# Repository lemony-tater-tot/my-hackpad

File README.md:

# my-hackpad
My hackpad made for hackclub stardance!

**Final Project design**

**Schematic**

**PCB Layout**

**Case**

# Bill of Materials (BOM)

| Part | Qty | Description / Specifications |
| :--- | :---: | :--- |
| **Seeed XIAO RP2040 microcontroller** | 1 | Main controller board |
| **EC11 rotary encoders (20mm D-shaft)** | 1 | Rotary input with integrated push-switch |
| **MX-style mechanical switches** | 3 | Key switches for macro inputs |
| **Blank DSA keycaps** | 3 | 1u profile keycaps for the mechanical switches |
| **Custom Macro Pad PCB** | 1 | Custom KiCad routed circuit board |
| **Switch Plate & Enclosure** | 1 | 3d printed top-plate / 3D printed housing |
| **M3×16mm screws** | 4 | Structural case assembly fasteners |
| **M3×5×4mm heatset inserts** | 4 | Brass inserts for secure case threading |

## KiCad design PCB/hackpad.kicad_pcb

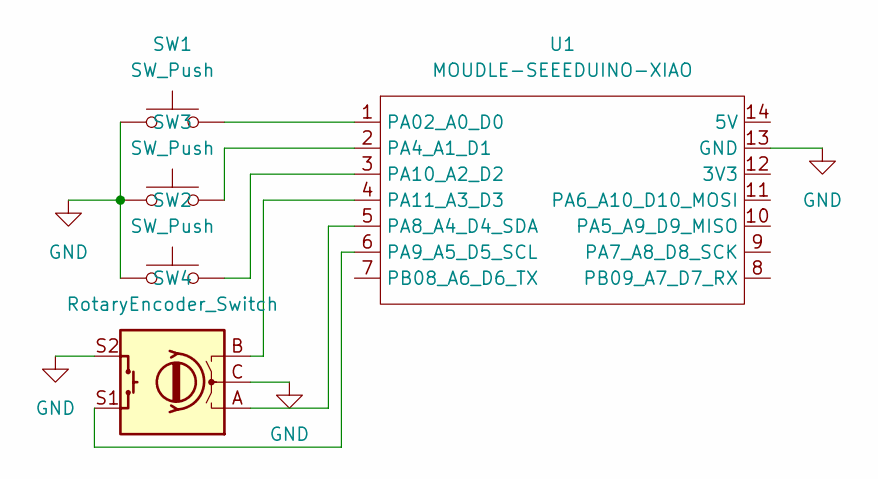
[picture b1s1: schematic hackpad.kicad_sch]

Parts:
SW1, SW2, SW3: SW_Push; SW_Cherry_MX_1.00u_PCB
SW4: RotaryEncoder_Switch; RotaryEncoder_Alps_EC11E-Switch_Vertical_H20mm
U1: MOUDLE-SEEEDUINO-XIAO; XIAO-Generic-Hybrid-14P-2.54-21X17.8MM

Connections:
GND: SW1.1, SW2.1, SW3.1, SW4.C, SW4.S2, U1.13 (GND)
unnamed: SW1.2, U1.1 (PA02_A0_D0)
unnamed: SW3.2, U1.2 (PA4_A1_D1)
unnamed: SW4.A, U1.5 (PA8_A4_D4_SDA)
unnamed: SW4.S1, U1.6 (PA9_A5_D5_SCL)
unnamed: SW2.2, U1.3 (PA10_A2_D2)
unnamed: SW4.B, U1.4 (PA11_A3_D3)

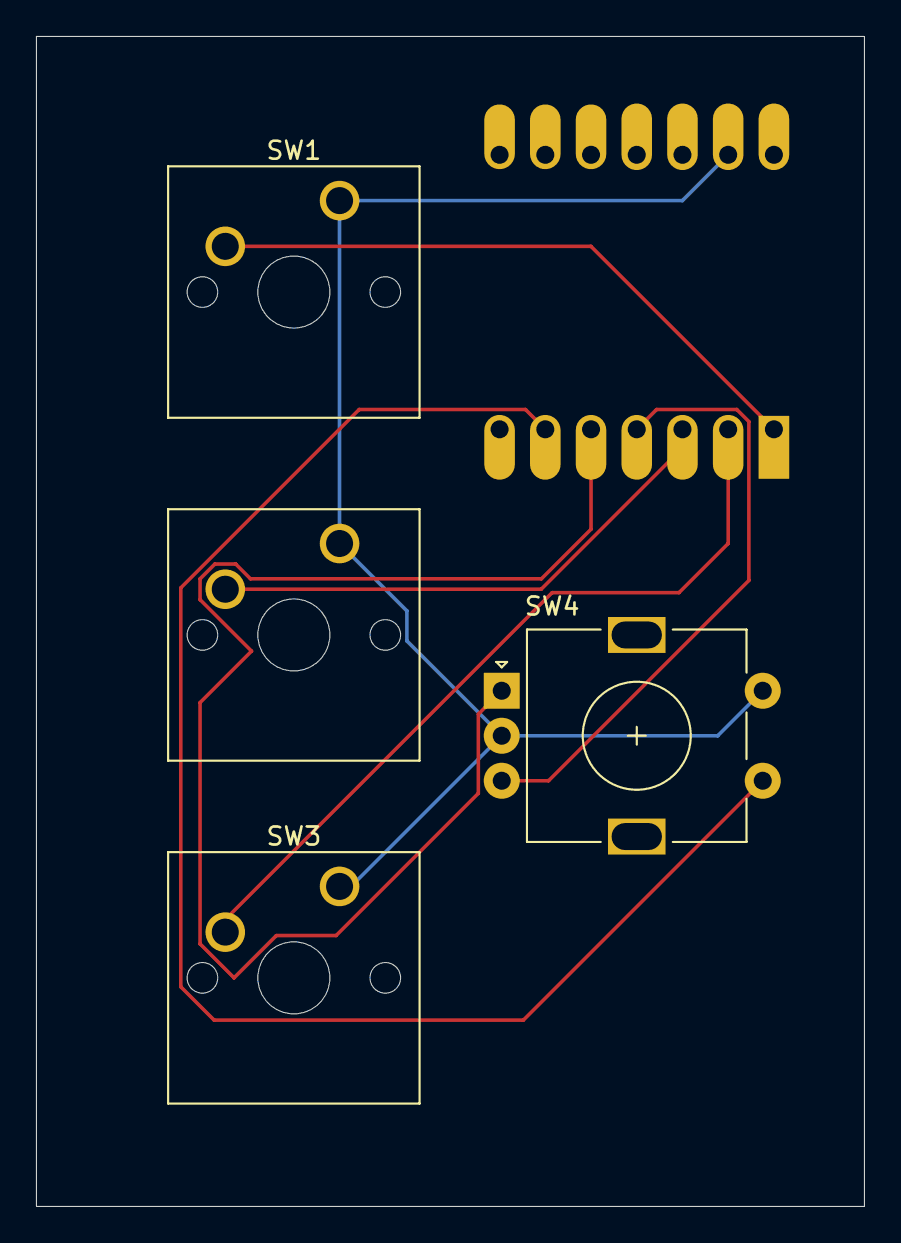
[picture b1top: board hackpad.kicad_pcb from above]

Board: 2 copper layers, 46.0 x 65.0 mm, 5 parts (1 on the bottom side), 7 nets.

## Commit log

2026-06-05 readme commit
2026-06-05 screenshot name cahnge
2026-06-05 Format
2026-06-05 add BOM
2026-06-05 add all project files
